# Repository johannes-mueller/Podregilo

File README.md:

# Podregilo

Arduino based hardware to control a podcasting DAW.

## Disclaimer

By now this project is far from being useful. It might be interesting to other developers though.

# Goal

We are developing and constructing an Arduino based hardware box to control our
DAW while podcasting. The following features are planned:

* mute buttons for all speakers

* buttons to start, stop and prepare the recording

* LED indications of the meter levels of the voices

* buttons to start jingles and other clips

* displaying the current time

# Status

## Prototypes

* First prototype on strip board

  The first prototype was soldered and wired completely manually on stripboards
  using magnet wire for every single comnnection. It was quite a tedious work
  building it but it has the advantage that we could test and develop it
  actually while building the first prototype. In the end the prototype worked
  but turned out to be far to unstable for serious work.

* Second prototype on an etched PCB.

  With what we've learned from the first prototype design, we designed the
  circuit in KiCad and then designed two PCBs, one for the front panel and one
  for the actual circuit. These PCBs we had produced by a professional PCB
  manufacturer. It turned out that we had some bugs in the circuit design which
  we for the second prototype fixed using a grinding tool and again a bit of
  magnet wire.

## Current Status

Right now we have the second prototype up and running and plan to use it in
actual everyday podcasting for a couple of months. Depending on our experiences
we will either have new PCBs produced or we will add some features, that need
hardware modifications.

# Used technology

The hardware is build around an Arduino compatible board, probably the Arduino
nano. We are using parallel shift registers SN74HC165 and SN74HC595 to get and
set the states of our hardware items. On the software side we speak OSC to our
DAW and also probably MIDI to other software. The meter levels we get via
jack. The software is written in python.

# Aimed platform

We are developing on Linux/Ardour. It shouldn't be too difficult to port the
stuff to Mac/Ardour or even Mac/Reaper.

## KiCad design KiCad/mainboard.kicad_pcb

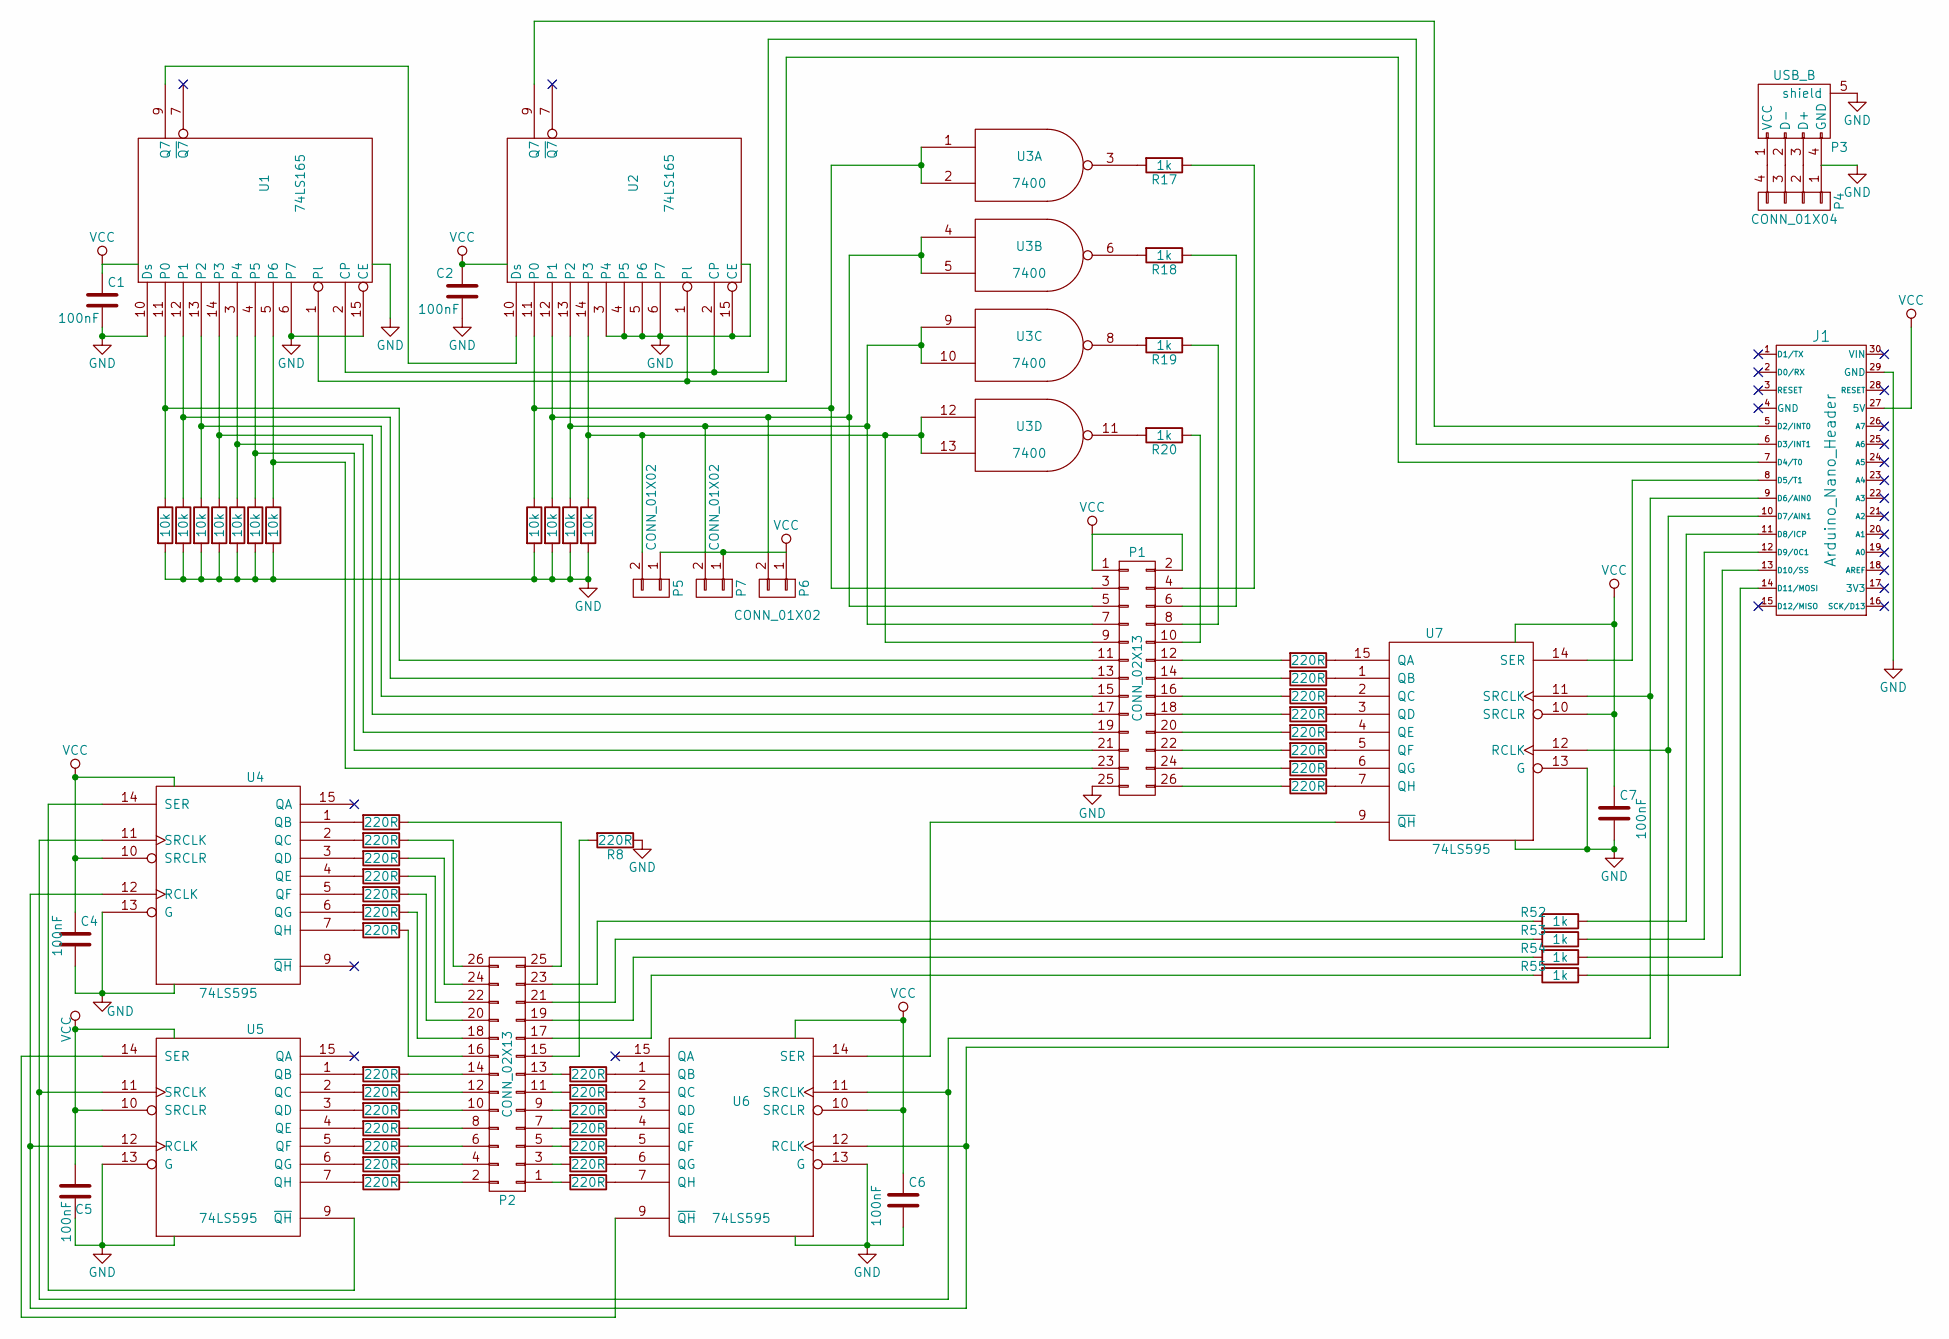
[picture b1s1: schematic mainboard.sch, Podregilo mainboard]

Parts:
C1, C2, C4, C5, C6, C7: 100nF; C_Disc_D3_P2.5
J1: Arduino_Nano_Header; arduino_nano_header
P1, P2: CONN_02X13; Pin_Header_Straight_2x13
P3: USB_B
P4: CONN_01X04; Pin_Header_Straight_1x04
P5, P6, P7: CONN_01X02; Pin_Header_Straight_1x02
R1, R2, R3, R4, R5, R6, R7, R13, R14, R15, R16: 10k; Resistor_Horizontal_RM7mm
R8, R21, R22, R23, R24, R25, R26, R27, R29, R30, R31, R32, R33, R34, R35, R37, R38, R39, R40, R41, R42, R43, R44, R45, R46, R47, R48, R49, R50, R51: 220R; Resistor_Horizontal_RM7mm
R17, R18, R19, R20, R52, R53, R54, R55: 1k; Resistor_Horizontal_RM7mm
U1, U2: 74LS165; DIP-16_W7.62mm
U3: 7400; DIP-14_W7.62mm
U4, U5, U6, U7: 74LS595; DIP-16_W7.62mm

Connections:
GND: C1.2, C2.2, C4.2, C5.1, C6.2, C7.2, J1.29 (GND), P1.25, P3.4 (GND), P3.5 (shield), P4.1, R1.2, R2.2, R3.2, R4.2, R5.2, R6.2, R7.2, R8.1, R13.2, R14.2, R15.2, R16.2, U1.6 (P7), U1.8 (GND), U1.10 (Ds), U1.15 (CE), U2.3 (P4), U2.4 (P5), U2.5 (P6), U2.6 (P7), U2.8 (GND), U2.15 (CE), U3.7 (GND), U4.8 (GND), U4.13 (G), U5.8 (GND), U5.13 (G), U6.8 (GND), U6.13 (G), U7.8 (GND), U7.13 (G)
unnamed: J1.5 (D2/INT0), U2.9 (Q7)
unnamed: J1.6 (D3/INT1), U1.2 (CP), U2.2 (CP)
unnamed: J1.7 (D4/T0), U1.1 (Pl), U2.1 (Pl)
unnamed: J1.8 (D5/T1), U7.14 (SER)
unnamed: J1.9 (D6/AIN0), U4.11 (SRCLK), U5.11 (SRCLK), U6.11 (SRCLK), U7.11 (SRCLK)
unnamed: J1.10 (D7/AIN1), U4.12 (RCLK), U5.12 (RCLK), U6.12 (RCLK), U7.12 (RCLK)
unnamed: J1.11 (D8/ICP), R52.1
unnamed: J1.12 (D9/0C1), R53.1
unnamed: J1.13 (D10/SS), R54.1
unnamed: J1.14 (D11/MOSI), R55.1
unnamed: P1.3, R13.1, U2.11 (P0), U3.1, U3.2
unnamed: P1.4, R17.1
unnamed: P1.5, P6.2, R14.1, U2.12 (P1), U3.4, U3.5
unnamed: P1.6, R18.1
unnamed: P1.7, P7.2, R15.1, U2.13 (P2), U3.9, U3.10
unnamed: P1.8, R19.1
unnamed: P1.9, P5.2, R16.1, U2.14 (P3), U3.12, U3.13
unnamed: P1.10, R20.1
unnamed: P1.11, R1.1, U1.11 (P0)
unnamed: P1.12, R44.2
unnamed: P1.13, R2.1, U1.12 (P1)
unnamed: P1.14, R45.2
unnamed: P1.15, R3.1, U1.13 (P2)
unnamed: P1.16, R46.2
unnamed: P1.17, R4.1, U1.14 (P3)
unnamed: P1.18, R47.2
unnamed: P1.19, R5.1, U1.3 (P4)
unnamed: P1.20, R48.2
unnamed: P1.21, R6.1, U1.4 (P5)
unnamed: P1.22, R49.2
unnamed: P1.23, R7.1, U1.5 (P6)
unnamed: P1.24, R50.2
unnamed: P1.26, R51.2
unnamed: P2.1, R43.2
unnamed: P2.2, R35.1
unnamed: P2.3, R42.2
unnamed: P2.4, R34.1
unnamed: P2.5, R41.2
unnamed: P2.6, R33.1
unnamed: P2.7, R40.2
unnamed: P2.8, R32.1
unnamed: P2.9, R39.2
unnamed: P2.10, R31.1
unnamed: P2.11, R38.2
unnamed: P2.12, R30.1
unnamed: P2.13, R37.2
unnamed: P2.14, R29.1
unnamed: P2.15, R8.2
unnamed: P2.16, R27.1
unnamed: P2.17, R55.2
unnamed: P2.18, R26.1
unnamed: P2.19, R54.2
unnamed: P2.20, R25.1
unnamed: P2.21, R53.2
unnamed: P2.22, R24.1
unnamed: P2.23, R52.2
unnamed: P2.24, R23.1
unnamed: P2.25, R21.1
unnamed: P2.26, R22.1
unnamed: P3.1 (VCC), P4.4
unnamed: P3.2 (D-), P4.3
unnamed: P3.3 (D+), P4.2
unnamed: R17.2, U3.3
unnamed: R18.2, U3.6
unnamed: R19.2, U3.8
unnamed: R20.2, U3.11
unnamed: R21.2, U4.1 (QB)
unnamed: R22.2, U4.2 (QC)
unnamed: R23.2, U4.3 (QD)
unnamed: R24.2, U4.4 (QE)
unnamed: R25.2, U4.5 (QF)
unnamed: R26.2, U4.6 (QG)
unnamed: R27.2, U4.7 (QH)
unnamed: R29.2, U5.1 (QB)
unnamed: R30.2, U5.2 (QC)
unnamed: R31.2, U5.3 (QD)
unnamed: R32.2, U5.4 (QE)
unnamed: R33.2, U5.5 (QF)
unnamed: R34.2, U5.6 (QG)
unnamed: R35.2, U5.7 (QH)
unnamed: R37.1, U6.1 (QB)
unnamed: R38.1, U6.2 (QC)
unnamed: R39.1, U6.3 (QD)
unnamed: R40.1, U6.4 (QE)
unnamed: R41.1, U6.5 (QF)
unnamed: R42.1, U6.6 (QG)
unnamed: R43.1, U6.7 (QH)
unnamed: R44.1, U7.15 (QA)
unnamed: R45.1, U7.1 (QB)
unnamed: R46.1, U7.2 (QC)
unnamed: R47.1, U7.3 (QD)
unnamed: R48.1, U7.4 (QE)
unnamed: R49.1, U7.5 (QF)
unnamed: R50.1, U7.6 (QG)
unnamed: R51.1, U7.7 (QH)
unnamed: U1.9 (Q7), U2.10 (Ds)
unnamed: U4.14 (SER), U5.9 (~QH)
unnamed: U5.14 (SER), U6.9 (~QH)
unnamed: U6.14 (SER), U7.9 (~QH)
VCC: C1.1, C2.1, C4.1, C5.2, C6.1, C7.1, J1.27 (5V), P1.1, P1.2, P5.1, P6.1, P7.1, U1.16 (VCC), U2.16 (VCC), U3.14 (VCC), U4.10 (SRCLR), U4.16 (VCC), U5.10 (SRCLR), U5.16 (VCC), U6.10 (SRCLR), U6.16 (VCC), U7.10 (SRCLR), U7.16 (VCC)

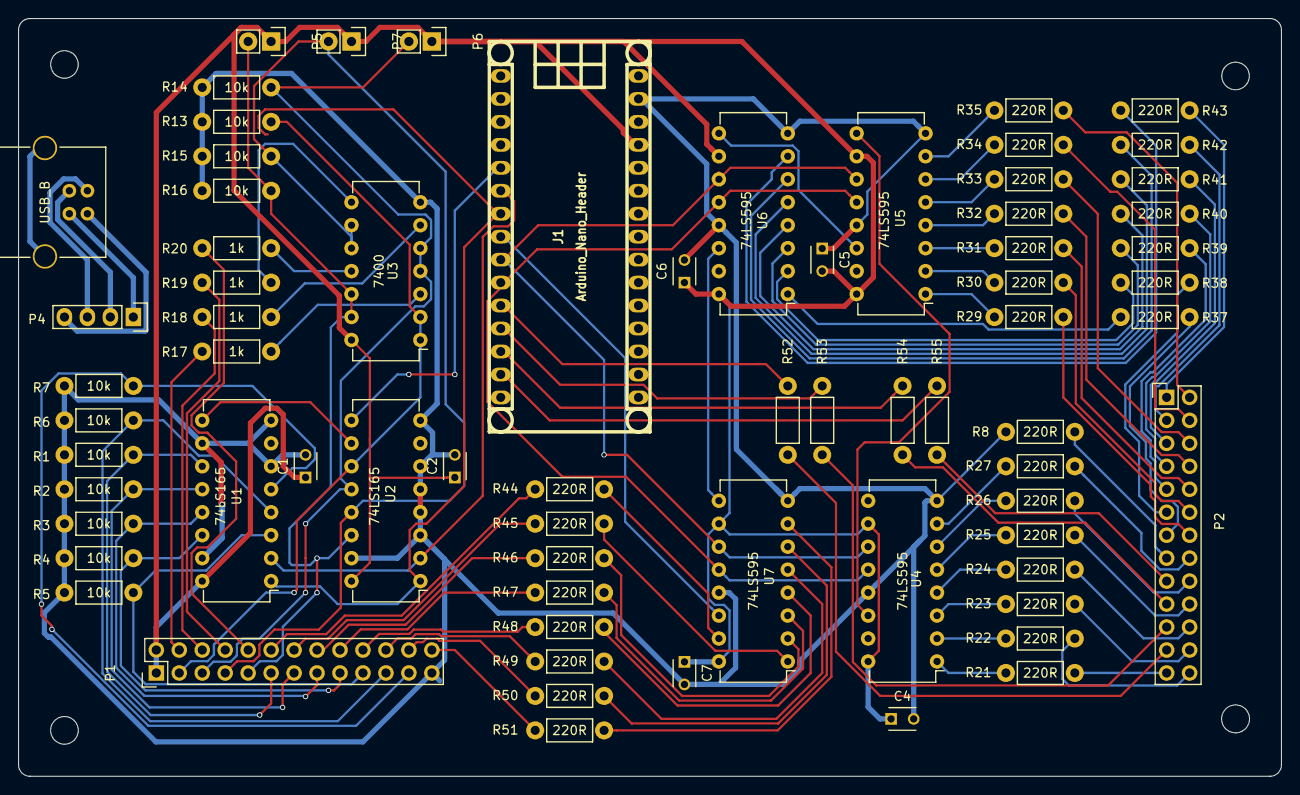
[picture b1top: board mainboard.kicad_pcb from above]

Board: 2 copper layers, 139.7 x 83.8 mm, 70 parts (0 on the bottom side), 101 nets.

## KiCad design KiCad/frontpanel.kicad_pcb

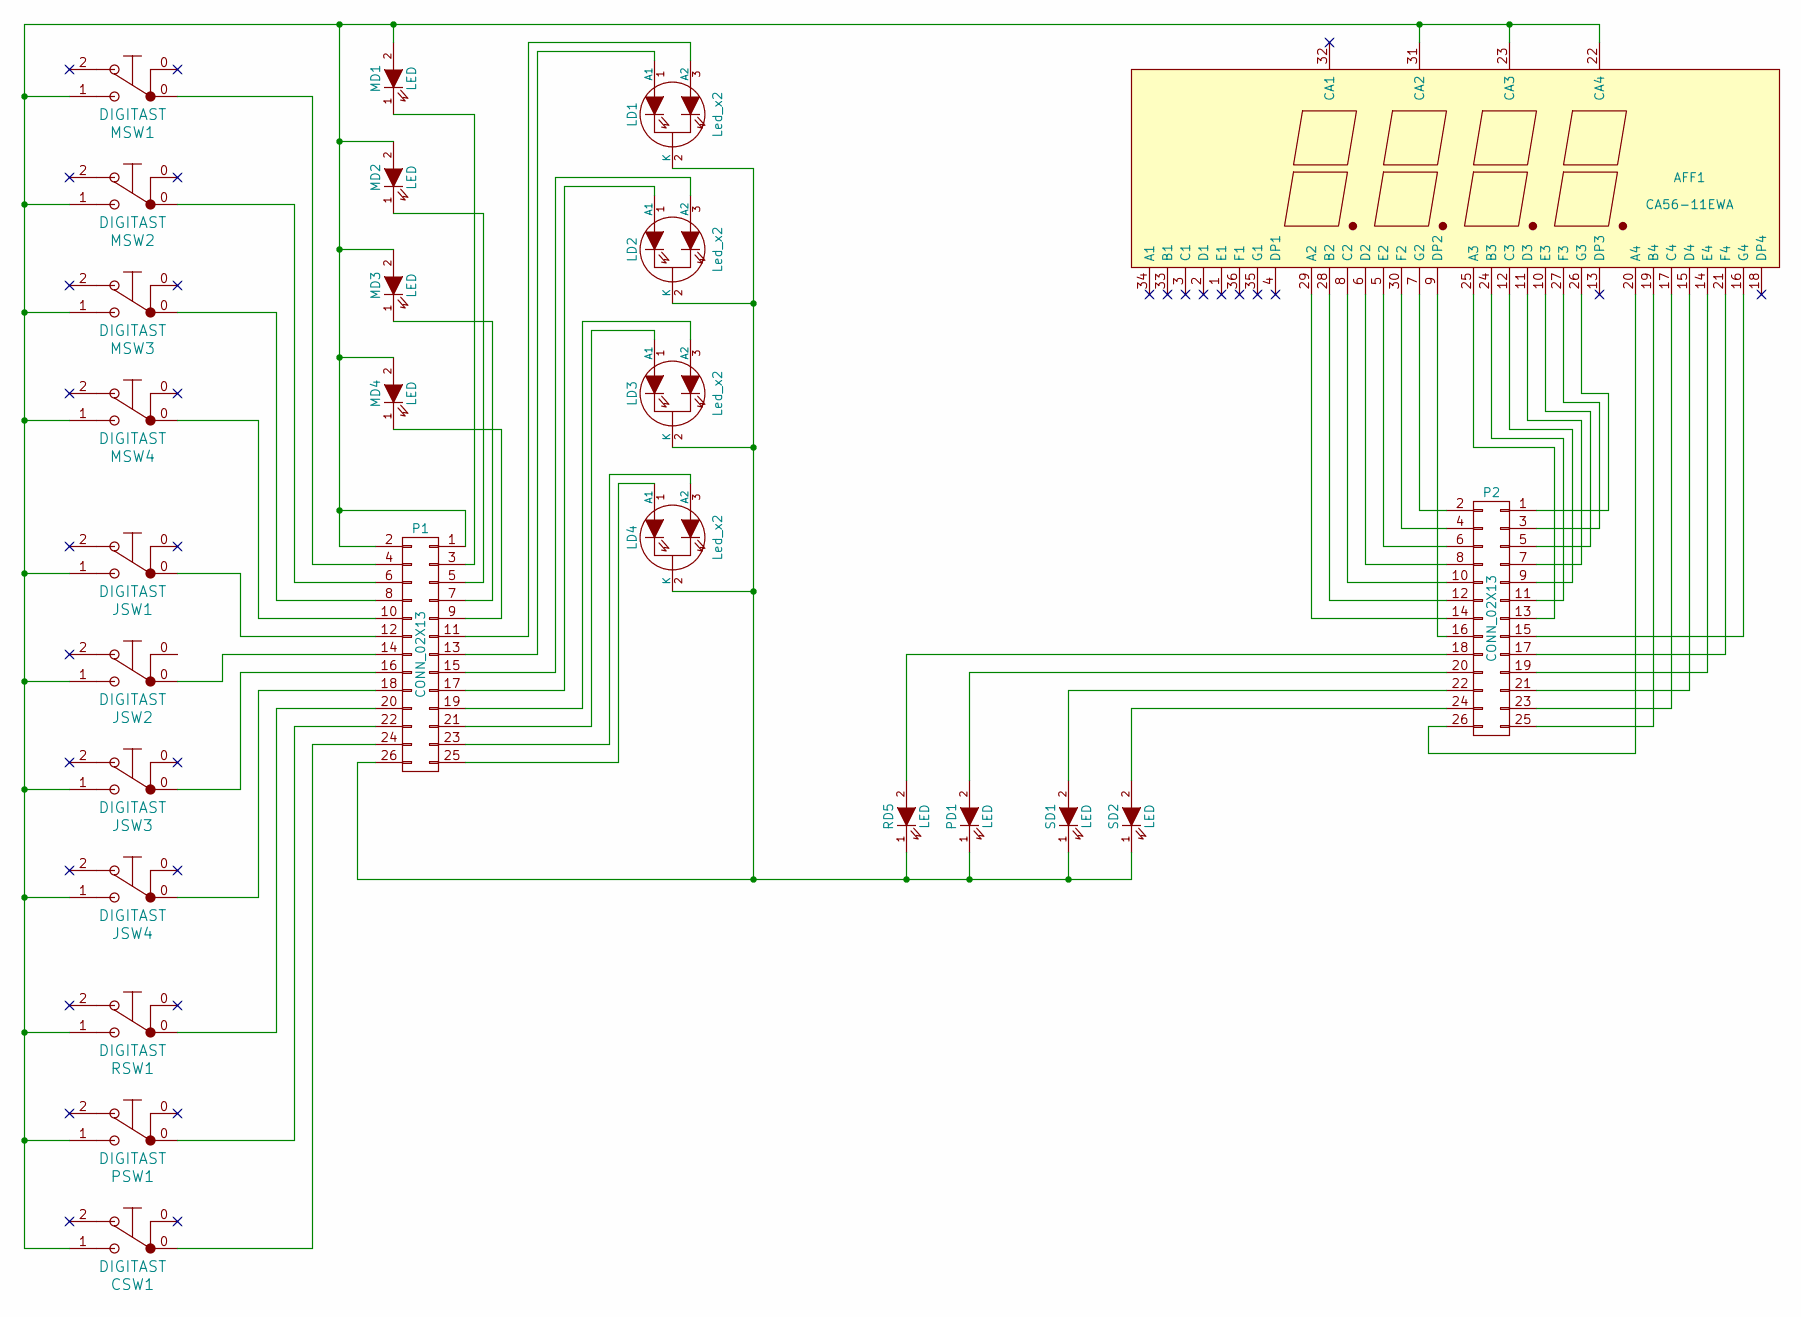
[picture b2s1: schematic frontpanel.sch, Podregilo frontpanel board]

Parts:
AFF1: CA56-11EWA; Cx56-11
CSW1: DIGITAST; SW-DIGITAST_modified
JSW1, JSW2, JSW3, JSW4: DIGITAST; SW-DIGITAST_modified
LD1, LD2, LD3, LD4: Led_x2; LED-RGB-5MM_Common_Cathode
MD1, MD2, MD3, MD4: LED; LED-3MM
MSW1, MSW2, MSW3, MSW4: DIGITAST; SW-DIGITAST_modified
P1, P2: CONN_02X13; Pin_Header_Straight_2x13
PD1: LED; LED-3MM
PSW1: DIGITAST; SW-DIGITAST_modified
RD5: LED; LED-3MM
RSW1: DIGITAST; SW-DIGITAST_modified
SD1, SD2: LED; LED-5MM

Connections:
unnamed: AFF1.5 (E2), P2.6
unnamed: AFF1.6 (D2), P2.8
unnamed: AFF1.7 (G2), P2.2
unnamed: AFF1.8 (C2), P2.10
unnamed: AFF1.9 (DP2), P2.16
unnamed: AFF1.10 (E3), P2.5
unnamed: AFF1.11 (D3), P2.7
unnamed: AFF1.12 (C3), P2.9
unnamed: AFF1.14 (E4), P2.19
unnamed: AFF1.15 (D4), P2.21
unnamed: AFF1.16 (G4), P2.15
unnamed: AFF1.17 (C4), P2.23
unnamed: AFF1.19 (B4), P2.25
unnamed: AFF1.20 (A4), P2.26
unnamed: AFF1.21 (F4), P2.17
unnamed: AFF1.22 (CA4), AFF1.23 (CA3), AFF1.31 (CA2), CSW1.1, JSW1.1, JSW2.1, JSW3.1, JSW4.1, MD1.2 (A), MD2.2 (A), MD3.2 (A), MD4.2 (A), MSW1.1, MSW2.1, MSW3.1, MSW4.1, P1.1, P1.2, PSW1.1, RSW1.1
unnamed: AFF1.24 (B3), P2.11
unnamed: AFF1.25 (A3), P2.13
unnamed: AFF1.26 (G3), P2.1
unnamed: AFF1.27 (F3), P2.3
unnamed: AFF1.28 (B2), P2.12
unnamed: AFF1.29 (A2), P2.14
unnamed: AFF1.30 (F2), P2.4
unnamed: CSW1.0, P1.24
unnamed: JSW1.0, P1.12
unnamed: JSW2.0, P1.14
unnamed: JSW3.0, P1.16
unnamed: JSW4.0, P1.18
unnamed: LD1.1 (A1), P1.13
unnamed: LD1.2 (K), LD2.2 (K), LD3.2 (K), LD4.2 (K), P1.26, PD1.1 (K), RD5.1 (K), SD1.1 (K), SD2.1 (K)
unnamed: LD1.3 (A2), P1.11
unnamed: LD2.1 (A1), P1.17
unnamed: LD2.3 (A2), P1.15
unnamed: LD3.1 (A1), P1.21
unnamed: LD3.3 (A2), P1.19
unnamed: LD4.1 (A1), P1.25
unnamed: LD4.3 (A2), P1.23
unnamed: MD1.1 (K), P1.3
unnamed: MD2.1 (K), P1.5
unnamed: MD3.1 (K), P1.7
unnamed: MD4.1 (K), P1.9
unnamed: MSW1.0, P1.4
unnamed: MSW2.0, P1.6
unnamed: MSW3.0, P1.8
unnamed: MSW4.0, P1.10
unnamed: P1.20, RSW1.0
unnamed: P1.22, PSW1.0
unnamed: P2.18, RD5.2 (A)
unnamed: P2.20, PD1.2 (A)
unnamed: P2.22, SD1.2 (A)
unnamed: P2.24, SD2.2 (A)

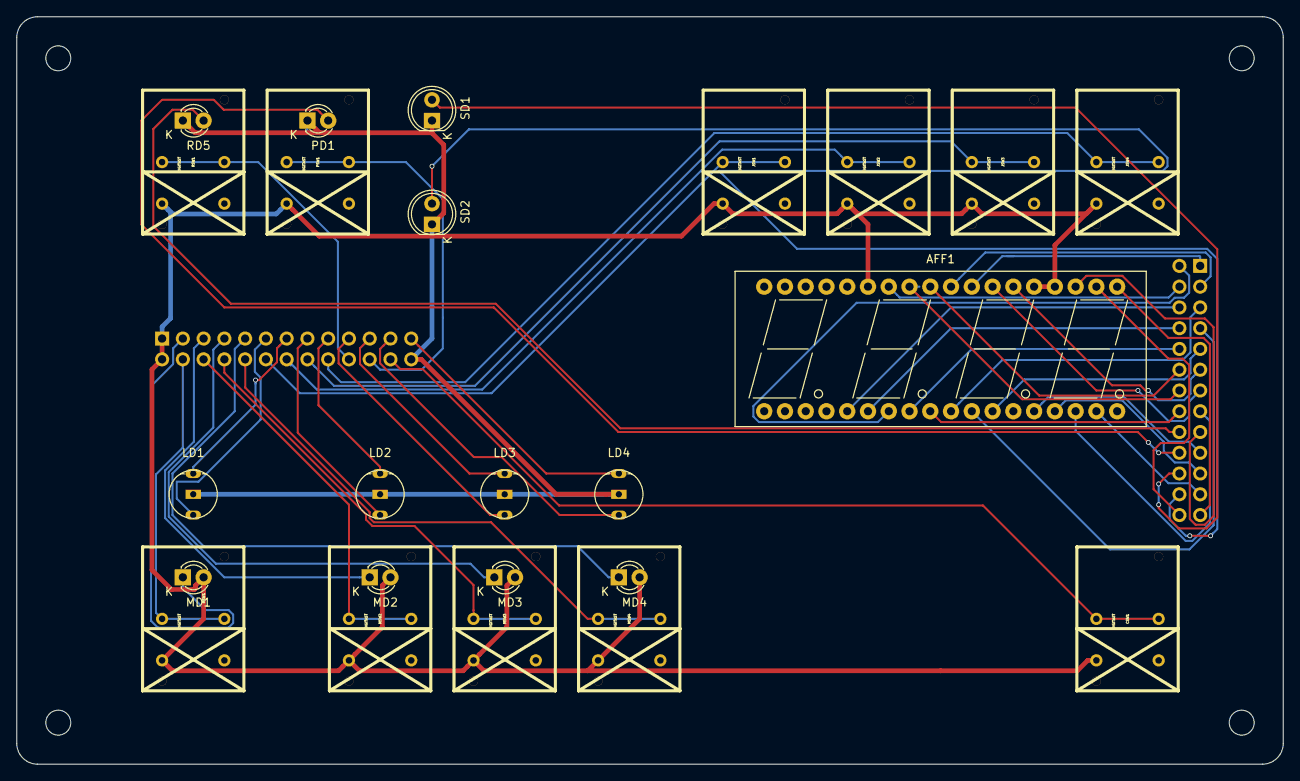
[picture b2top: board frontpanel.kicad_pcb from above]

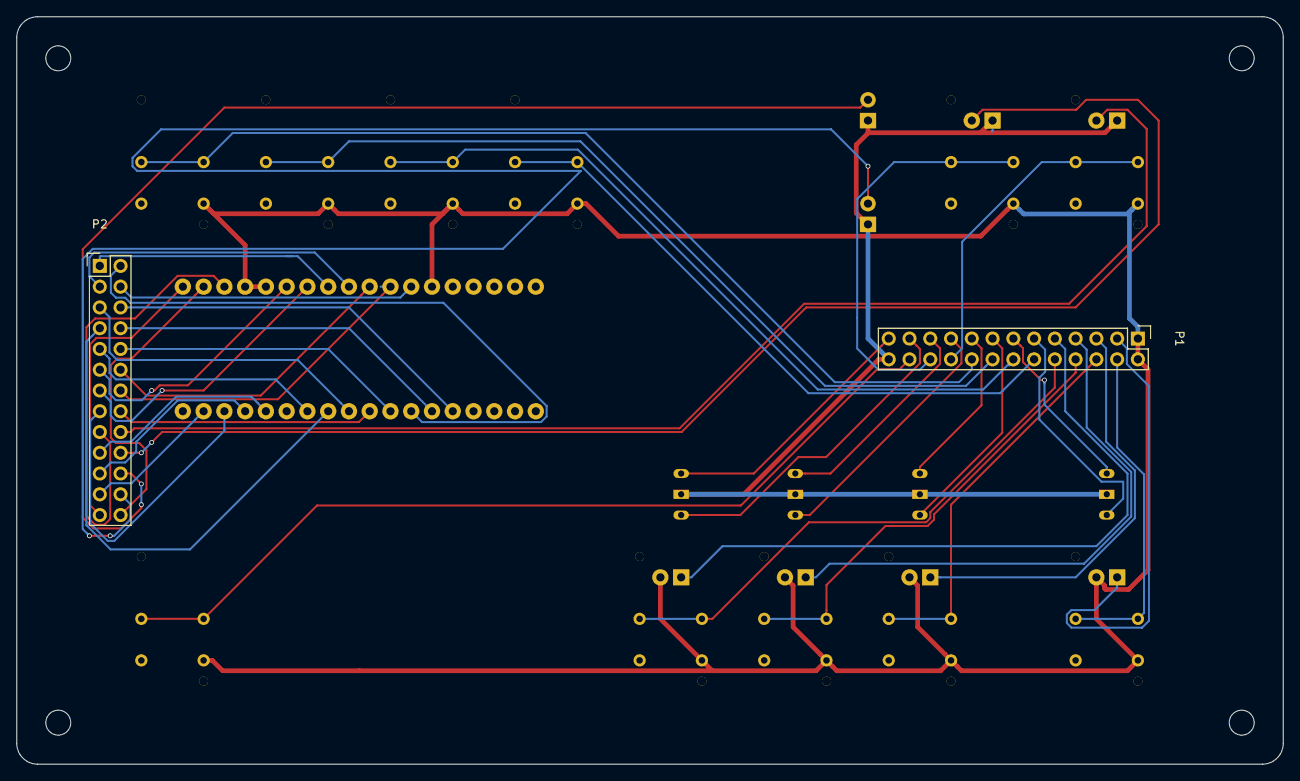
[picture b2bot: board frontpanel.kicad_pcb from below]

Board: 2 copper layers, 154.9 x 91.4 mm, 26 parts (2 on the bottom side), 51 nets.

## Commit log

2015-10-24 Initial commit
    Just a little bit to play with. Arduino/podregilo the program to be
    uploaded to Arduino. Python/podregilo is a python program to communicate
    with Arduino and with the DAW.
2015-10-24 Some work on handling the state data
    Now the incoming state byte is separated into a muting state and an
    "other" state. The muting state is handled on proof of concept level.
2015-10-24 Handling mute buttons properly
    Now mute buttons are triggering OSC messages to ardour. The ardour route
    ids (rids) must fit the number of the mute butten. Later we will make
    this configureble by a dict or something like that.
2015-10-24 Some work on the README.md
2015-10-24 Added copyright information to source files.
2015-10-25 Restored lost line of code
2015-10-25 Make it handle two bytes of button state data
    Using two shift registers we are able to read two bytes of button states
    and pass it via Serial to the python side. In python we split those 16
    bits of button states into 4 groups of 4 buttons. So we have 4 callback
    functions, that we can set, that can handle groups of four buttons.
2015-10-25 Prefer local static varibles over global variables
2015-10-25 Slightly smarte function name :)
2015-10-25 Slightly smarter function name :)
2015-10-26 Update README.md
    Typo
2015-10-26 Changed shift register pin variable names
    Later on we will have two shift register channels, one for input and one
    for output. So we need to sets of shift register pin variables.
2015-11-01 We use an Arduino nano 328.
2015-11-01 Changed the pins according to the actual setup.
2015-11-01 Adjusted pin variable names again.
2015-11-01 We need to wait for the second byte.
    Unfortunately we seem to receive two separate dataReceived events, when
    Arduino sends us two bytes. So we need to wait for the second event, if
    we notice, that we only have one byte.
2015-11-03 Started on drawing the circuit.
2015-11-04 Put a disclaimer line into README.md
2015-11-05 Ignore build files
2015-11-05 First steps of shifting out data.
2015-11-05 Make the code a bit nicer
2015-11-05 Get rid of type cast warning ...
2015-11-05 Implemented meter LED states
2015-11-05 Handle correct channel
2015-11-05 Make jack client deliver level data
2015-11-05 Shutdown LEDs when no more devel data is comming
2015-11-06 Simpler documentclass for the circuit design
2015-11-06 Flipped mute and jingle buttons
2015-11-06 Added arduinoNANO component.
2015-11-06 Introduced LED objects.
    LED is a struct, which describes the state of a LED. It comes with
    functions to switch it on or off or make it blink.
2015-11-06 Added diagnosis functionality
    Arduino now is probing the USB bus to check wether our computer app is
    respondig. It sets the diagnosis LEDs accodingly:
    * red: Waiting for response
    * red blink: timeout passed, still probing and hoping
    * green: response received: probing again every 10 seconds
2015-11-07 Some connections on the circuits
2015-11-09 First steps of control button LEDs and time display
2015-11-10 Minor code cleanup
    * some blank lines removed
    * removed unnecessary typedefs
2015-11-10 Implemented receiving new time code in Arduino
    ... not tested though. Will test it as soon as the signaling from python
    is ready.
2015-11-10 Some rudimentary tests and fixes in time update
    ... tested only by manual signaling using Serial Monitor.
2015-11-10 Documenting some global variables
2015-11-10 Make JackClient not start jackd ...
    ... but wait for it, if it's not there.
2015-11-10 First steps towards OSC communication
    ... took some code from txosc. Will send a pull request to txosc soon.
2015-11-11 Finished displaying time ...
2015-11-11 Rudimentary support for triggering play
2015-11-11 Implemented rudimentary jingle play support by MIDI
    ... needs to be changed to jack midi
2015-11-11 Reactivate connection control ...
2015-11-12 Using ToggleRoll instead of transport_play
    This allows us to start and also to stop the Ardour transport.
2015-11-12 Do not send NOTEOFF by default to MIDI
    And *never ever* use time.sleep() in a process that also is a jack client.
2015-11-12 Make the JackClient not cause latency
    Obviously the JackClient flooded the serial queue because it with evere
    process() call sends something to Arduino. Now we make the Arduino
    connection poll the level data from jack and jack only stores the
    maximum levels since the last poll.
2015-11-12 Changed the level treshholds
    ... still somewhat temporary ...
2015-11-12 Send non existing demand for #current_value
    In Ardour this current value query is currently ifd out. So this branch
    is a test, whether it works in principle, given that the feature is
    getting back to Ardour. As soon as the feature is back to Ardour we
    merge this branch into master.
2015-11-13 Implemented debuging channel and use of status LEDs.
2015-11-14 Implemented record prepare button
2015-11-14 Switch off button LEDs when connection is lost.
2015-11-14 Added remove-last-capture to record prepare ...
    ... found that Ardour has the global option of switching off the
    verification dialog of remove last capture.
2016-04-28 ignore *.pyc
2016-04-28 get rid of another strange file
2016-04-28 got rid of strange file
2016-04-28 Switch to KiCad
    The circuit is documented using KiCad rather than TikZ. This has the
    advantage that we can also develop the PDB inside the project.
    We have two pcbs: the mainboard and the frontpanel board.
2016-04-28 turned Arduino around
2016-04-29 some changes and improvments
2016-04-30 Flipped the pinpads on the frontpanel board ...
    ... so that we don't have to twist the cables.
2016-04-30 Reinforced power wires on frontpanel board
2016-04-30 stripped some wires
2016-04-30 adjusted frontpanel board size
2016-05-01 added some metainfo
2016-05-01 adjusted metadata
2017-01-07 Added four missing LED-resistors and ...
    ... turned Arduino again. That was necessary because the connector must not be
    at the edge of the PCB.
2017-01-07 Adjusted OSC commands to Ardour 5.x
2017-01-07 Adjusted pins to KiCad PCB
2017-01-07 Made CLK INH (Pin 15) of the 74HC165s LO
    The input shift registers turned out to have a strong tendency to disturbance
    and their signals were very unstable. The manual of 74HC165 says, that all
    the unused input pins should be either at GND or VCC. For the CLK INH
    (clock inhibit) VCC is not an option, as this would inhibit the clock.
    Therefore we put them to GND.
    It turns out to be far more stable.
2017-01-07 added missing connection
2017-01-07 The jingle buttens are actually on the 4th (3) byte
2017-01-07 corrected origin coordinates
2017-01-07 adjust pin numbers to kicad scheme
2017-01-07 Ignore Gerber and drill files
2017-01-07 fixed wrong led order
2017-01-07 Maybe the compiler also would optimize this :)
2017-01-08 Added decoupling capacitors to the ICs
2017-01-22 Implemented long press events
2017-06-02 Adjusted sensitivity of signal leds
2017-06-02 Added capacitors to ICs
2017-06-02 Implemented transport_speed reply
2017-06-02 Implemented long button presses on for the JinglePlayer
    The state LongPress during Looping is not handled properly.
    Hard to do though :(
2017-06-02 pass the gain value as float when muting
2017-06-02 First steps towarts OSC communication with Ardour
2017-06-02 Implemented mute buttons
2017-06-02 Made jackd's sample_rate accessible by jack_client::Proxy
2017-06-02 Created event::Queue, so we no longer need to clone event::Manager
2017-06-02 Introduced LevelEvent ...
    ... in order to show audio data on Podregilo's level LEDs.
2017-06-02 testa
2017-06-02 Record enabled signal from Ardour -> Arduino
2017-06-02 Introduced transport time event
2017-06-02 Changed the event architecture
2017-06-02 Generic function to pass events
2017-06-02 Slight code rearrangement for the sake of readability
2017-06-02 Introducet jack_client
2017-06-02 Make sure that we have received the sample rate ...
    ... when we return the jack_client::Proxy instance
2017-06-02 Slight code rearrangement
2017-06-02 First skeleton of CLI
2017-06-02 Prototyped registering event observers
2017-06-02 Make USB-path a CLI parameter
2017-06-02 Changes in event architecture
2017-06-02 Handover the JoinHandle of the Arduino thread to main()
2017-06-02 Make the event::Queue independent from event::Manager
    Otherwise it gets hard to get the lifetimes of interdependent resources strait.
2017-06-02 Why didn't they tell me earlier, that I can write this shorter?
2017-06-02 Changed command structure to handle long press events
2017-06-02 Make jack client properly quit
2017-06-05 Use the red LED to indicate xruns.
    The more xruns, the faster we blink
2019-01-04 KiCad update; wiring of denoising capacitors
2019-01-04 Rust update
